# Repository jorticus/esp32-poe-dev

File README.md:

## ESP32 PoE Dev Board

A simple ESP32 ethernet + PoE dev board

WARNING: PoE is NOT ISOLATED! Be careful what you attach.

See [jared.geek.nz/esp32-poe-devboard](jared.geek.nz/esp32-poe-devboard) for the story.

## Usage

### ESPHome

```yaml
esp32:
  board: esp32dev

ethernet:
  type:     RTL8201
  mdc_pin:  GPIO23
  mdio_pin: GPIO18
  clk_mode: GPIO0_OUT
  phy_addr: 0

...
```

### Arduino

`main.cpp`
```cpp
void setup() {
    // WiFi antenna not available on this board
    WiFi.mode(WIFI_OFF); 

    ETH.begin();
    ETH.config();
}
```

`platformio.ini`
```ini
[platformio]

[env:esp32_poe]
platform  = espressif32
framework = arduino
board     = esp32_dev
build_flags = 
    -DETH_PHY_ADDR=0
    -DETH_PHY_MDC=23
    -DETH_PHY_MDIO=18
    -DETH_PHY_TYPE=ETH_PHY_RTL8201
    -DETH_CLK_MODE=ETH_CLOCK_GPIO0_OUT

```

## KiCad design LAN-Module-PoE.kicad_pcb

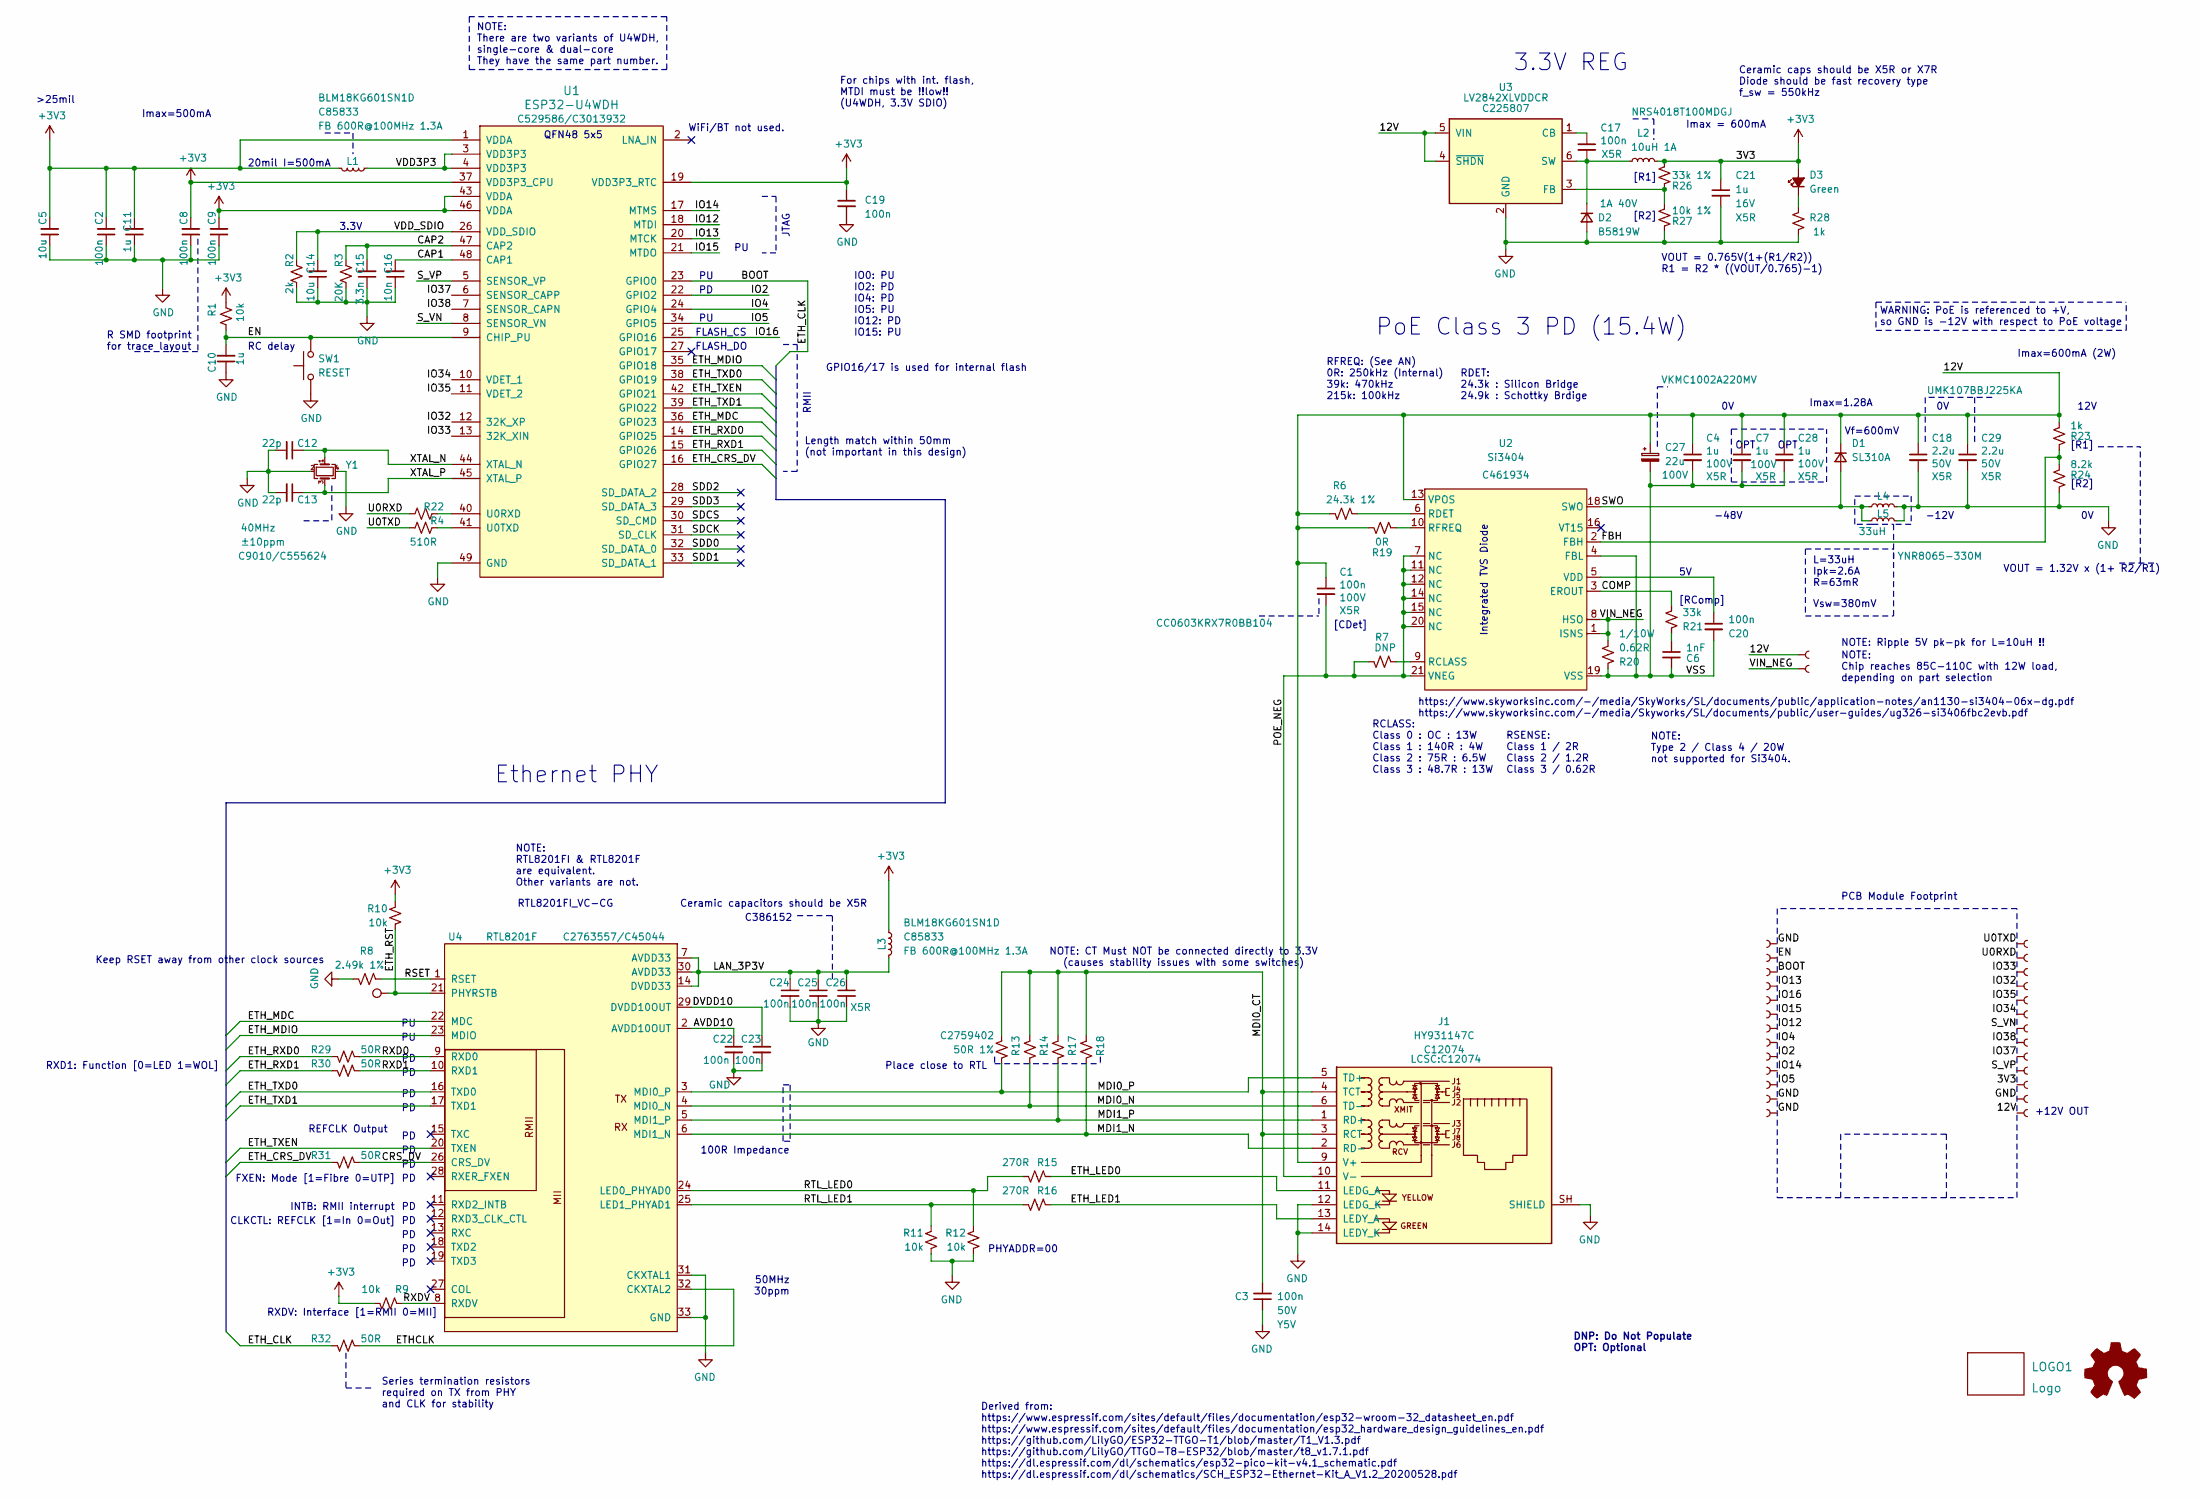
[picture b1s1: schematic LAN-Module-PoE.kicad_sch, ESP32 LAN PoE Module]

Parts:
C1: 100n; C_0603_1608Metric; Part CC0603KRX7R0BB104; LCSC C113803
C2, C3, C9, C17, C19, C20, C23, C24, C25, C26: 100n; C_0603_1608Metric
C4: 1u; C_0805_2012Metric; Part HMK212BC7105KGHTE; LCSC C385977
C5, C14: 10u; C_0603_1608Metric
C6: 1nF; C_0603_1608Metric
C7, C10, C11, C21, C28: 1u; C_0603_1608Metric
C8, C22: 100n; R_0603_1608Metric
C12, C13: 22p; C_0603_1608Metric
C15: 3.3n; C_0603_1608Metric
C16: 10n; C_0603_1608Metric
C18, C29: 2.2u; C_0805_2012Metric; Part UMK107BBJ225KA; LCSC C268016
C27: 22u; C_Elec_6.3x5.4; Part VKMC1002A220MV; LCSC C487431
D1: SL310A; D_SMA
D2: B5819W; D_SOD-123; Rating 1A 40V; LCSC C2685454
D3: Green; LED_0603_1608Metric
J1: HY931147C; RJ45_Wuerth_7499111446_Horizontal; Part LCSC:C12074; LCSC C12074
J2, J3, J4, J5, J6, J7, J8, J9, J10, J11, J12, J13, J14, J15, J16, J17, J18, J19, J20, J21, J22, J23, J24, J25, J26, J27, J28, J29: ProtoCastellatedHeader; ProtoHeader_65mil
L1, L3: FB 600R@100MHz 1.3A; R_0603_1608Metric; Part BLM18KG601SN1D; LCSC C85833
L2: 10uH 1A; L_Taiyo-Yuden_NR-40xx; Part NRS4018T100MDGJ; LCSC C222882
L4: 33uH; L_Taiyo-Yuden_NR-80xx_HandSoldering; Rating 1.2A; Part YNR8065-330M; LCSC C2681905
L5: -; L_Taiyo-Yuden_NR-60xx
LOGO1: Logo; wolfpaw-0.3
R1, R9, R10, R11, R12: 10k; R_0603_1608Metric
R2: 2k; R_0603_1608Metric
R3: 20K; R_0603_1608Metric
R4, R22: 510R; R_0603_1608Metric
R6: 24.3k 1%; R_0603_1608Metric; LCSC C2930079
R7: DNP; R_0603_1608Metric
R8: 2.49k 1%; R_0603_1608Metric; LCSC C2930072
R13: 50R 1%; R_0603_1608Metric; Tolerance 1%; LCSC C2759402
R14, R17: 50R 1%; R_0603_1608Metric; Tolerance 1%
R15, R16: 270R; R_0603_1608Metric
R18: 50R 1%; R_0603_1608Metric
R19: 0R; R_0603_1608Metric
R20: 0.62R; R_0805_2012Metric; LCSC C2930222
R21: 33k; R_0603_1608Metric
R23: 1k; R_0603_1608Metric; LCSC C22548
R24: 8.2k; R_0603_1608Metric; LCSC C114637
R26: 33k 1%; R_0603_1608Metric; LCSC C126359
R27: 10k 1%; R_0603_1608Metric; LCSC C98220
R28: 1k; R_0603_1608Metric
R29, R30, R31, R32: 50R; R_0603_1608Metric
SW1: RESET; SW_Push_SPST_NO_Alps_SKRK
TP1: TP; TP-1MM
U1: ESP32-U4WDH; QFN-48-1EP_5x5mm_P0.35mm_EP3.7x3.7mm_ThermalVias; LCSC C529586/C3013932
U2: Si3404; QFN-20-1EP_4x4mm_P0.5mm_EP2.6x2.6mm; LCSC C461934
U3: LV2842XLVDDCR; SOT-23-6; LCSC C225807
U4: RTL8201F; QFN-32-1EP_5x5mm_P0.5mm_EP3.1x3.1mm; LCSC C2763557/C45044
Y1: 40MHz; Crystal_SMD_3225-4Pin_3.2x2.5mm; LCSC C9010/C555624

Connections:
+3V3: C2.2, C5.2, C8.2, C9.2, C11.2, C19.1, C21.1, D3.2 (A), J15.1, L1.2, L2.2, L3.1, R1.2, R9.1, R10.1, R26.2, U1.1 (VDDA), U1.19 (VDD3P3_RTC), U1.37 (VDD3P3_CPU), U1.43 (VDDA), U1.46 (VDDA)
/12V: C1.1, C4.1, C7.1, C18.1, C27.1, C28.1, C29.1, D1.1 (K), J1.9 (V+), J2.1, J28.1, R6.1, R19.1, R23.2, U2.13 (VPOS), U3.4 (~SHDN), U3.5 (VIN)
/AVDD10: C22.1, U4.2 (AVDD10OUT)
/BOOT: J5.1, R32.1, U1.23 (GPIO0)
/CAP1: C16.2, U1.48 (CAP1)
/CAP2: C15.2, R3.2, U1.47 (CAP2)
/COMP: R21.2, U2.3 (EROUT)
/CRS_DV: R31.2, U4.26 (CRS_DV)
/DVDD10: C23.1, U4.29 (DVDD10OUT)
/EN: C10.2, J4.1, R1.1, SW1.2, U1.9 (CHIP_PU)
/ETHCLK: R32.2, U4.32 (CKXTAL2)
/ETH_CRS_DV: R31.1, U1.16 (GPIO27)
/ETH_LED0: J1.11 (LEDG_A), R15.2
/ETH_LED1: J1.13 (LEDY_A), R16.2
/ETH_MDC: U1.36 (GPIO23), U4.22 (MDC)
/ETH_MDIO: U1.35 (GPIO18), U4.23 (MDIO)
/ETH_RST: R10.2, TP1.1, U4.21 (PHYRSTB)
/ETH_RXD0: R29.1, U1.14 (GPIO25)
/ETH_RXD1: R30.1, U1.15 (GPIO26)
/ETH_TXD0: U1.38 (GPIO19), U4.16 (TXD0)
/ETH_TXD1: U1.39 (GPIO22), U4.17 (TXD1)
/ETH_TXEN: U1.42 (GPIO21), U4.20 (TXEN)
/FBH: R23.1, R24.2, U2.2 (FBH)
/IO2: J11.1, U1.22 (GPIO2)
/IO4: J10.1, U1.24 (GPIO4)
/IO5: J13.1, U1.34 (GPIO5)
/IO12: J9.1, U1.18 (MTDI)
/IO13: J6.1, U1.20 (MTCK)
/IO14: J12.1, U1.17 (MTMS)
/IO15: J8.1, U1.21 (MTDO)
/IO16: J7.1, U1.25 (GPIO16)
/IO32: J20.1, U1.12 (32K_XP)
/IO33: J19.1, U1.13 (32K_XIN)
/IO34: J22.1, U1.10 (VDET_1)
/IO35: J21.1, U1.11 (VDET_2)
/IO37: J25.1, U1.6 (SENSOR_CAPP)
/IO38: J24.1, U1.7 (SENSOR_CAPN)
/LAN_3P3V: C24.1, C25.1, C26.1, L3.2, U4.7 (AVDD33), U4.14 (DVDD33), U4.30 (AVDD33)
/MDI0_CT: C3.2, J1.3 (RCT), J1.4 (TCT), R13.1, R14.1, R17.1, R18.1
/MDI0_N: J1.6 (TD-), R14.2, U4.4 (MDI0_N)
/MDI0_P: J1.5 (TD+), R13.2, U4.3 (MDI0_P)
/MDI1_N: J1.2 (RD-), R18.2, U4.6 (MDI1_N)
/MDI1_P: J1.1 (RD+), R17.2, U4.5 (MDI1_P)
/POE_NEG: C1.2, J1.10 (V-), R7.1, U2.7 (NC), U2.11 (NC), U2.12 (NC), U2.14 (NC), U2.15 (NC), U2.20 (NC), U2.21 (VNEG)
/RSET: R8.2, U4.1 (RSET)
/RTL_LED0: R12.1, R15.1, U4.24 (LED0_PHYAD0)
/RTL_LED1: R11.1, R16.1, U4.25 (LED1_PHYAD1)
/RXD0: R29.2, U4.9 (RXD0)
/RXD1: R30.2, U4.10 (RXD1)
/RXDV: R9.2, U4.8 (RXDV)
/SDCK: U1.31 (SD_CLK)
/SDCS: U1.30 (SD_CMD)
/SDD0: U1.32 (SD_DATA_0)
/SDD1: U1.33 (SD_DATA_1)
/SDD2: U1.28 (SD_DATA_2)
/SDD3: U1.29 (SD_DATA_3)
/SWO: D1.2 (A), L4.1, L5.1, U2.18 (SWO)
/S_VN: J23.1, U1.8 (SENSOR_VN)
/S_VP: J26.1, U1.5 (SENSOR_VP)
/U0RXD: J18.1, R22.1
/U0TXD: J17.1, R4.1
/VDD3P3: L1.1, U1.3 (VDD3P3), U1.4 (VDD3P3)
/VDD_SDIO: C14.2, R2.2, U1.26 (VDD_SDIO)
/VIN_NEG: J29.1, R20.2, U2.1 (ISNS), U2.8 (HSO)
/VSS: C4.2, C6.2, C7.2, C20.2, C27.2, C28.2, R20.1, U2.4 (FBL), U2.19 (VSS)
/XTAL_N: C12.1, U1.44 (XTAL_N), Y1.1
/XTAL_P: C13.1, U1.45 (XTAL_P), Y1.3
GND: C2.1, C3.1, C5.1, C8.1, C9.1, C10.1, C11.1, C12.2, C13.2, C14.1, C15.1, C16.1, C18.2, C19.2, C21.2, C22.2, C23.2, C24.2, C25.2, C26.2, C29.2, D2.2 (A), J1.12 (LEDG_K), J1.14 (LEDY_K), J1.SH (SHIELD), J3.1, J14.1, J16.1, J27.1, L4.2, L5.2, R2.1, R3.1, R8.1, R11.2, R12.2, R24.1, R27.1, R28.1, SW1.1, U1.49 (GND), U3.2 (GND), U4.31 (CKXTAL1), U4.33 (GND), Y1.2, Y1.4
unnamed: C6.1, R21.1
unnamed: C17.2, D2.1 (K), L2.1, U3.6 (SW)
unnamed: D3.1 (K), R28.2
unnamed: R22.2, U1.40 (U0RXD)
unnamed: R4.2, U1.41 (U0TXD)
unnamed: R7.2, U2.9 (RCLASS)
unnamed: R6.2, U2.6 (RDET)
unnamed: R19.2, U2.10 (RFREQ)
unnamed: C20.1, U2.5 (VDD)
unnamed: C17.1, U3.1 (CB)
unnamed: R26.1, R27.2, U3.3 (FB)

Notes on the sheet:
3.3V
IO0: PU IO2: PD IO4: PD IO5: PU IO12: PD IO15: PU
QFN48 5x5
50MHz 30ppm
https://www.skyworksinc.com/-/media/SkyWorks/SL/documents/public/application-notes/an1130-si3404-06x-dg.pdf https://www.skyworksinc.com/-/media/Skyworks/SL/documents/public/user-guides/ug326-si3406fbc2evb.pdf
OPT
Keep RSET away from other clock sources
12V
Derived from: https://www.espressif.com/sites/default/files/documentation/esp32-wroom-32_datasheet_en.pdf https://www.espressif.com/sites/default/files/documentation/esp32_hardware_design_guidelines_en.pdf https://github.com/LilyGO/ESP32-TTGO-T1/blob/master/T1_V1.3.pdf https://github.com/LilyGO/TTG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
I=500mA
RDET: 24.3k : Silicon Bridge 24.9k : Schottky Brdige
Vsw=380mV
Integrated TVS Diode
>25mil
-12V
Ceramic caps should be X5R or X7R Diode should be fast recovery type f_sw = 550kHz
WiFi/BT not used.
+12V OUT
GPIO16/17 is used for internal flash
20mil
NOTE: Ripple 5V pk-pk for L=10uH !!
[R1]
DNP: Do Not Populate OPT: Optional
[RComp]
C386152
NOTE: There are two variants of U4WDH, single-core & dual-core They have the same part number.
NOTE: CT Must NOT be connected directly to 3.3V (causes stability issues with some switches)
Series termination resistors required on TX from PHY and CLK for stability
Ceramic capacitors should be X5R
Imax = 600mA
Imax=600mA (2W)
NOTE: Type 2 / Class 4 / 20W not supported for Si3404.
PCB Module Footprint
RC delay
[R2]
RXD1: Function [0=LED 1=WOL]
RSENSE: Class 1 / 2R Class 2 / 1.2R Class 3 / 0.62R
INTB: RMII interrupt
RCLASS: Class 0 : OC : 13W Class 1 : 140R : 4W Class 2 : 75R : 6.5W Class 3 : 48.7R : 13W
FLASH_CS

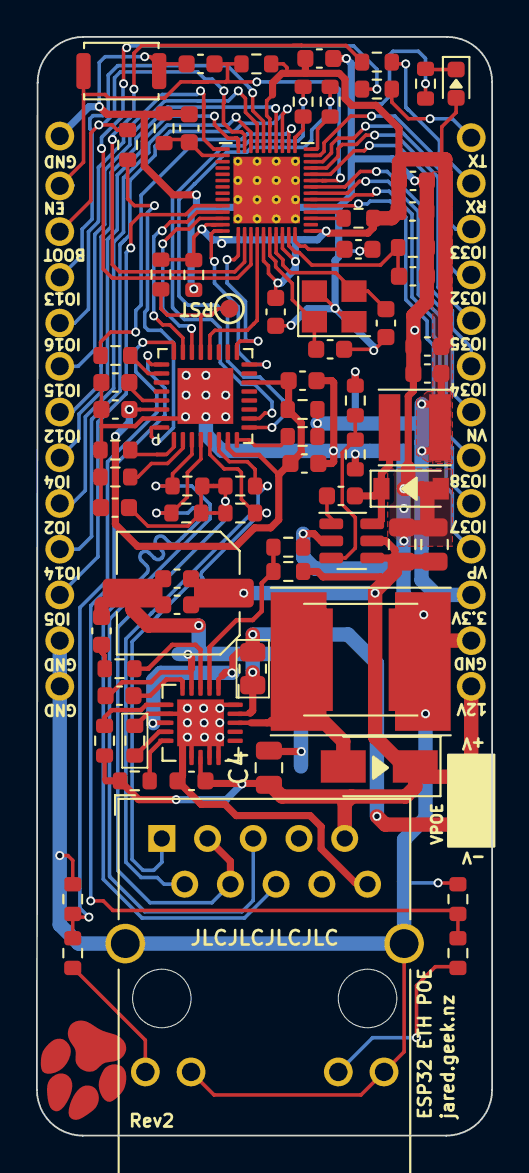
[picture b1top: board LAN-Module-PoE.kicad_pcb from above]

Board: 2 copper layers, 25.3 x 61.0 mm, 104 parts (0 on the bottom side), 73 nets.

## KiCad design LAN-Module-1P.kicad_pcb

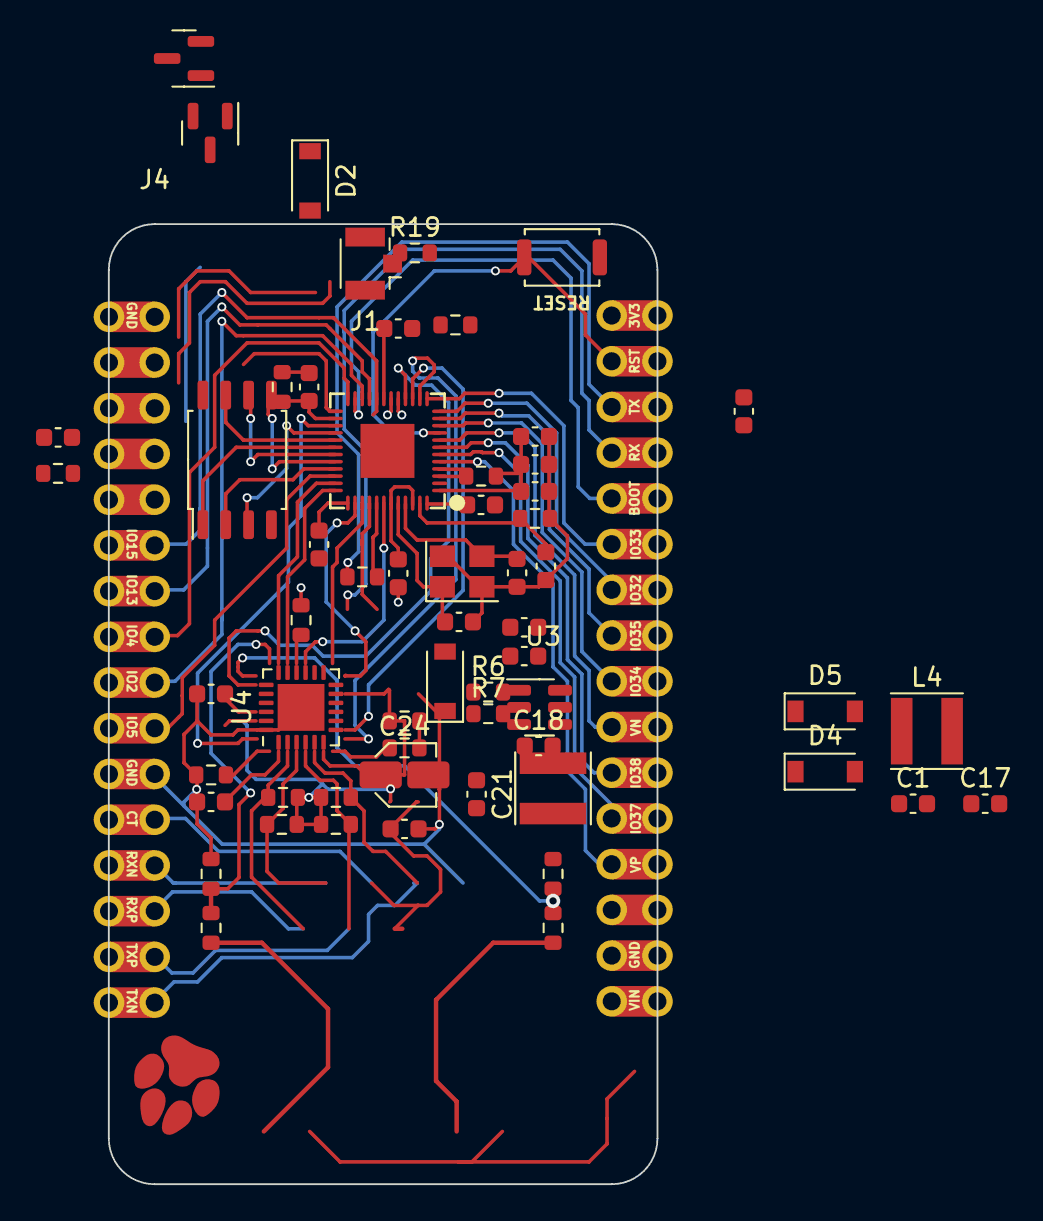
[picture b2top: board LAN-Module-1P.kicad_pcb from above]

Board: 2 copper layers, 30.5 x 53.3 mm, 62 parts (0 on the bottom side), 50 nets.

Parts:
C1, C5, C6, C7, C17, C19, C22, C23: 100n; C_0603_1608Metric
C2, C8, C9: 1u; C_0603_1608Metric
C3, C4: 10u; C_0603_1608Metric
C10, C11: 22p; C_0603_1608Metric
C12: 4.7u; C_0603_1608Metric
C13, C15: 3.3n; C_0603_1608Metric
C14, C16: 10n; C_0603_1608Metric
C18, C21: 2.2u; C_0603_1608Metric
C24: 4.7u; C_Elec_3x5.4
D1, D2, D4, D5: FM240W; D_SOD-123
J1: ANT; U.FL_Hirose_U.FL-R-SMT-1_Vertical
J4: Conn_Left; ProtoCastellatedHeader_1x16
J5: Conn_Right; ProtoCastellatedHeader_1x16
L1, L3: FB 600R@100MHz 1.3A; R_0603_1608Metric
L2, L4: 10uH 1A; L_Taiyo-Yuden_NR-40xx
LOGO1: Logo; wolfpaw-0.3
Q1, Q2: 2N7002; SOT-23
R1, R5, R6, R10, R11, R12, R15: 10k; R_0603_1608Metric
R2: 2k; R_0603_1608Metric
R3: 20K; R_0603_1608Metric
R4: 2.49k 1%; R_0603_1608Metric
R7, R8: 499R; R_0603_1608Metric
R9: 10K; R_0603_1608Metric
R13: 22k; R_0603_1608Metric
R14: 47k; R_0603_1608Metric
R16: 33k 1%; R_0603_1608Metric
R17: 10k 1%; R_0603_1608Metric
R18, R19: 0R; R_0603_1608Metric
SW1: RESET; SW_Push_SPST_NO_Alps_SKRK
U1: ESP32-U4WDH; ESP32-REDUCED
U2: W25Q32; SOIC-8_5.23x5.23mm_P1.27mm
U3: LV2842XLVDDCR; SOT-23-6
U4: CP2102N-Axx-xQFN24; QFN-24-1EP_4x4mm_P0.5mm_EP2.6x2.6mm
Y1: 40MHz ±10ppm; Crystal_SMD_3225-4Pin_3.2x2.5mm

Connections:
+3V3: C1.2, C2.2, C3.2, C4.2, C5.2, C6.2, C7.2, C9.2, C17.1, C19.1, C22.2, C24.1, L1.2, L2.2, L4.2, R1.2, R9.2, R15.2, R16.1, U1.1 (VDDA), U1.19 (VDD3P3_RTC), U1.37 (VDD3P3_CPU), U1.43 (VDDA), U1.46 (VDDA), U2.8 (VCC), U4.5 (VIO), U4.6 (VDD), U4.7 (VREGIN)
/BOOT: J5.5, R18.2, U1.23 (GPIO0)
/CAP1: C14.2, C16.2, U1.48 (CAP1)
/CAP2: C13.2, C15.2, R3.2, U1.47 (CAP2)
/EN: C8.2, J5.2, R1.1, R19.2, SW1.2, U1.9 (CHIP_PU)
/ETH_RST: R6.2, R10.2
/IO2: J4.9, U1.22 (GPIO2)
/IO4: J4.8, U1.24 (GPIO4)
/IO5: J4.10, U1.34 (GPIO5)
/IO12: J4.3, R9.1, U1.18 (MTDI)
/IO13: J4.6, U1.20 (MTCK)
/IO14: J4.4, U1.17 (MTMS)
/IO15: J4.7, U1.21 (MTDO)
/IO16: J4.2, U1.25 (GPIO16)
/IO32: J5.7, U1.12 (32K_XP)
/IO33: J5.6, U1.13 (32K_XIN)
/IO34: J5.9, U1.10 (VDET_1)
/IO35: J5.8, U1.11 (VDET_2)
/IO37: J5.12, U1.6 (SENSOR_CAPP)
/IO38: J5.11, U1.7 (SENSOR_CAPN)
/SDCK: U1.31 (SD_CLK), U2.6 (CLK)
/SDCS: U1.30 (SD_CMD), U2.1 (~CS)
/SDD0: U1.32 (SD_DATA_0), U2.5 (DI(IO0))
/SDD1: U1.33 (SD_DATA_1), U2.2 (DO(IO1))
/SDD2: U1.28 (SD_DATA_2), U2.3 (IO2)
/SDD3: U1.29 (SD_DATA_3), U2.7 (IO3)
/S_VN: J5.10, U1.8 (SENSOR_VN)
/S_VP: J5.13, U1.5 (SENSOR_VP)
/U0RXD: J5.4, R7.1, U4.21 (TXD)
/U0TXD: J5.3, R8.1, U4.20 (RXD)
/VDD3P3: L1.1, U1.3 (VDD3P3), U1.4 (VDD3P3)
/VDD_SDIO: C12.2, R2.2, U1.26 (VDD_SDIO)
/XTAL_N: C10.1, U1.44 (XTAL_N), Y1.1
/XTAL_P: C11.1, U1.45 (XTAL_P), Y1.3
GND: C1.1, C2.1, C3.1, C4.1, C5.1, C6.1, C7.1, C8.1, C9.1, C10.2, C11.2, C12.1, C13.1, C14.1, C15.1, C16.1, C17.2, C18.2, C19.2, C21.2, C22.1, C24.2, D1.2 (A), D5.2 (A), J1.2 (Ext), J4.1, J4.11, J5.15, R2.1, R3.1, R4.1, R11.2, R12.2, R14.1, R17.2, SW1.1, U1.49 (GND), U2.4 (GND), U3.2 (GND), U4.2 (GND), U4.25 (GND), Y1.2, Y1.4
unnamed: D1.1 (K), L2.1
unnamed: C23.1, U3.1 (CB)
unnamed: C23.2, D5.1 (K), L4.1, U3.6 (SW)
unnamed: J1.1 (In), U1.2 (LNA_IN)
unnamed: Q1.1 (G), Q2.2 (S), U4.19 (~RTS)
unnamed: Q1.2 (S), R18.1
unnamed: Q1.3 (D), Q2.1 (G), U4.23 (~DTR)
unnamed: Q2.3 (D), R19.1
unnamed: R7.2, U1.40 (U0RXD)
unnamed: R8.2, U1.41 (U0TXD)
unnamed: R13.1, R14.2, U4.8 (VBUS)
unnamed: R15.1, U4.9 (~RST)
unnamed: R16.2, R17.1, U3.3 (FB)
VBUS: D2.2 (A), D4.2 (A), R13.2
VDD: C18.1, C21.1, D2.1 (K), D4.1 (K), L3.1, R5.1, R6.1, R10.1, U3.4 (~SHDN), U3.5 (VIN)

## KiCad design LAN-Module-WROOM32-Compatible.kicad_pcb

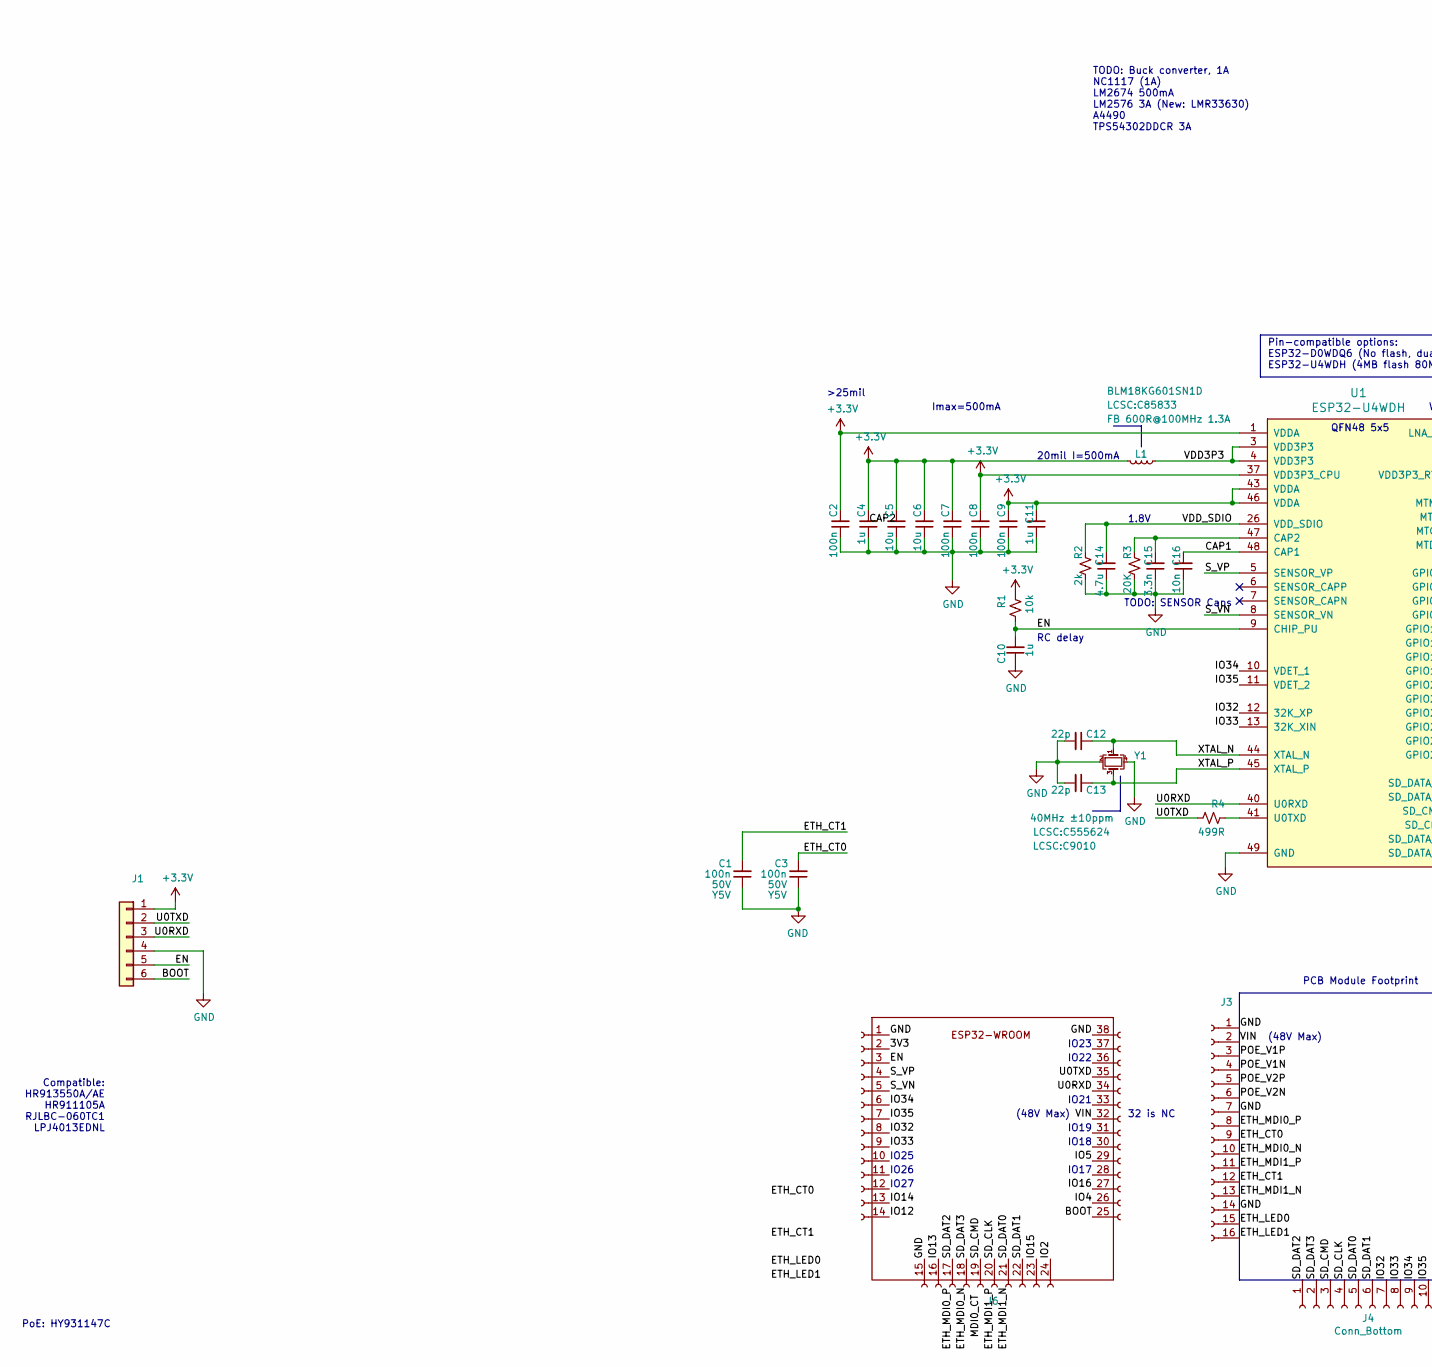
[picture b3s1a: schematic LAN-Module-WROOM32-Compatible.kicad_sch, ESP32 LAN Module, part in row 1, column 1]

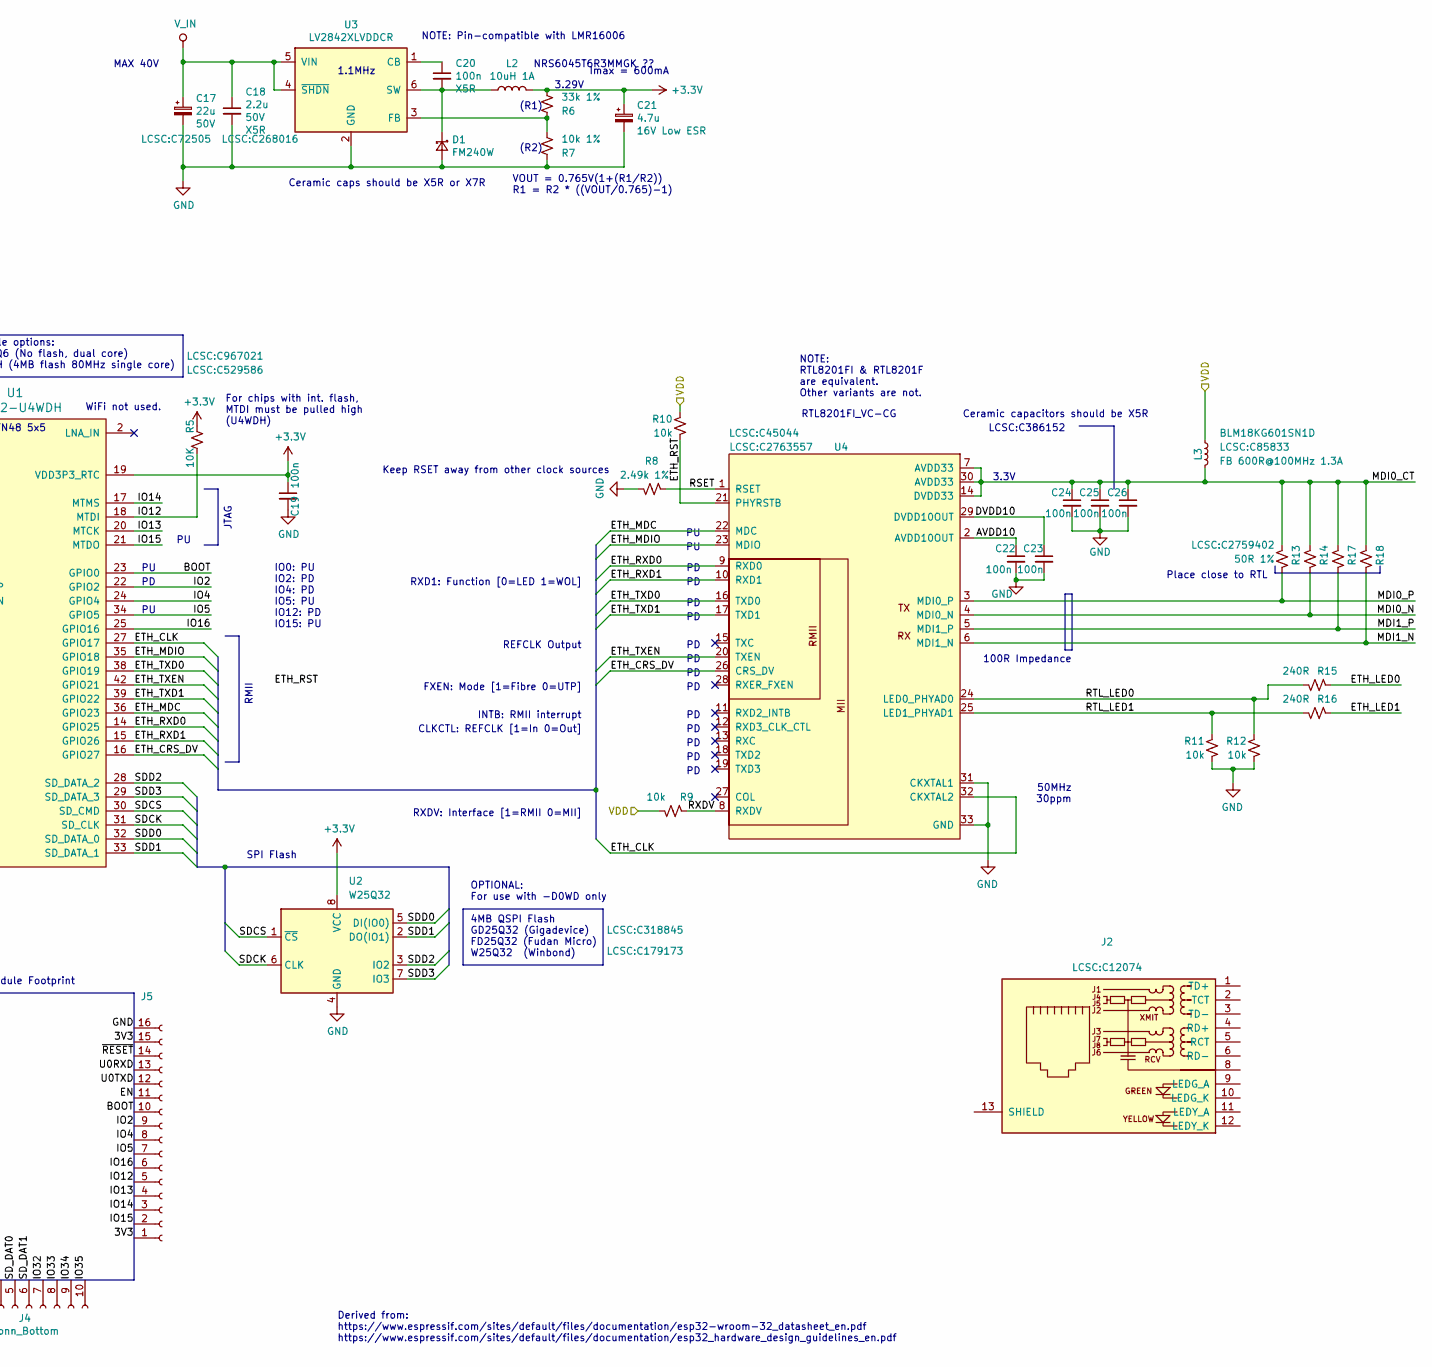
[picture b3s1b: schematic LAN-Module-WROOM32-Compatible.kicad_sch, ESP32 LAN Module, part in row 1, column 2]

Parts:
C1, C3: 100n; C_0603_1608Metric; Rating 50V
C2, C7, C8, C9, C19, C20, C22, C23, C24, C25, C26: 100n; C_0603_1608Metric
C4, C10, C11: 1u; C_0805_2012Metric
C5, C6: 10u; C_Elec_3x5.4
C12, C13: 22p; C_0603_1608Metric
C14, C21: 4.7u; C_Elec_3x5.4
C15: 3.3n; C_0603_1608Metric
C16: 10n; C_0603_1608Metric
C17: 22u; C_Elec_6.3x5.4; Part1 LCSC:C72505
C18: 2.2u; C_0603_1608Metric; Part1 LCSC:C268016
D1: FM240W; D_SMA
J1, J3, J5, J6: (no value)
J2: Part LCSC:C12074
J4: Conn_Bottom
L1, L3: FB 600R@100MHz 1.3A; R_0805_2012Metric_Pad1.20x1.40mm_HandSolder; Part1 LCSC:C85833
L2: 10uH 1A; L_Taiyo-Yuden_NR-40xx
R1, R9, R10, R11, R12: 10k; R_0603_1608Metric
R2: 2k; R_0603_1608Metric
R3: 20K; R_0603_1608Metric
R4: 499R; R_0603_1608Metric
R5: 10K; R_0603_1608Metric
R6: 33k 1%; R_0603_1608Metric
R7: 10k 1%; R_0603_1608Metric
R8: 2.49k 1%; R_0603_1608Metric
R13: 50R 1%; R_0603_1608Metric; Part LCSC:C2759402
R14, R17, R18: 49.9R 1%; R_0603_1608Metric
R15, R16: 240R; R_0603_1608Metric
U1: ESP32-U4WDH; ESP32-REDUCED; Part1 LCSC:C529586
U2: W25Q32; SOIC-8_5.23x5.23mm_P1.27mm; Part LCSC:C179173
U3: LV2842XLVDDCR; SOT-23-6
U4: Part1 LCSC:C2763557
Y1: 40MHz ±10ppm; Crystal_SMD_3225-4Pin_3.2x2.5mm_HandSoldering; Part1 LCSC:C9010

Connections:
+3V3: C2.2, C4.2, C5.2, C6.2, C7.2, C8.2, C9.2, C11.2, C19.1, C21.1, J1.1, L1.2, L2.2, R1.2, R5.2, R6.1, U1.1 (VDDA), U1.19 (VDD3P3_RTC), U1.37 (VDD3P3_CPU), U1.43 (VDDA), U1.46 (VDDA), U2.8 (VCC)
/3V3: J5.1, J5.15, J6.2
/AVDD10: C22.1, U4.2 (AVDD10OUT)
/BOOT: J1.6, J5.10, J6.25, U1.23 (GPIO0)
/CAP1: C16.2, U1.48 (CAP1)
/DVDD10: C23.1, U4.29 (DVDD10OUT)
/EN: C10.2, J1.5, J5.11, J6.3, R1.1, U1.9 (CHIP_PU)
/ETH_CLK: U1.27 (GPIO17), U4.32 (CKXTAL2)
/ETH_CRS_DV: U1.16 (GPIO27), U4.26 (CRS_DV)
/ETH_CT0: C3.2, J3.9
/ETH_CT1: C1.2, J3.12
/ETH_LED0: J3.15, R15.2
/ETH_LED1: J3.16, R16.2
/ETH_MDC: U1.36 (GPIO23), U4.22 (MDC)
/ETH_MDI0_N: J3.10
/ETH_MDI0_P: J3.8
/ETH_MDI1_N: J3.13
/ETH_MDI1_P: J3.11
/ETH_MDIO: U1.35 (GPIO18), U4.23 (MDIO)
/ETH_RST: R10.2, U4.21 (PHYRSTB)
/ETH_RXD0: U1.14 (GPIO25), U4.9 (RXD0)
/ETH_RXD1: U1.15 (GPIO26), U4.10 (RXD1)
/ETH_TXD0: U1.38 (GPIO19), U4.16 (TXD0)
/ETH_TXD1: U1.39 (GPIO22), U4.17 (TXD1)
/ETH_TXEN: U1.42 (GPIO21), U4.20 (TXEN)
/IO2: J5.9, J6.24, U1.22 (GPIO2)
/IO4: J5.8, J6.26, U1.24 (GPIO4)
/IO5: J5.7, J6.29, U1.34 (GPIO5)
/IO12: J5.5, J6.14, R5.1, U1.18 (MTDI)
/IO13: J5.4, J6.16, U1.20 (MTCK)
/IO14: J5.3, J6.13, U1.17 (MTMS)
/IO15: J5.2, J6.23, U1.21 (MTDO)
/IO16: J5.6, J6.27, U1.25 (GPIO16)
/IO32: J4.7, J6.8, U1.12 (32K_XP)
/IO33: J4.8, J6.9, U1.13 (32K_XIN)
/IO34: J4.9, J6.6, U1.10 (VDET_1)
/IO35: J4.10, J6.7, U1.11 (VDET_2)
/MDI0_CT: C24.1, C25.1, C26.1, L3.2, R13.1, R14.1, R17.1, R18.1, U4.7 (AVDD33), U4.14 (DVDD33), U4.30 (AVDD33)
/MDI0_N: R14.2, U4.4 (MDI0_N)
/MDI0_P: R13.2, U4.3 (MDI0_P)
/MDI1_N: R18.2, U4.6 (MDI1_N)
/MDI1_P: R17.2, U4.5 (MDI1_P)
/POE_V1N: J3.4
/POE_V1P: J3.3
/POE_V2N: J3.6
/POE_V2P: J3.5
/RSET: R8.2, U4.1 (RSET)
/RTL_LED0: R12.1, R15.1, U4.24 (LED0_PHYAD0)
/RTL_LED1: R11.1, R16.1, U4.25 (LED1_PHYAD1)
/RXDV: R9.2, U4.8 (RXDV)
/SDCK: U1.31 (SD_CLK), U2.6 (CLK)
/SDCS: U1.30 (SD_CMD), U2.1 (~CS)
/SDD0: U1.32 (SD_DATA_0), U2.5 (DI(IO0))
/SDD1: U1.33 (SD_DATA_1), U2.2 (DO(IO1))
/SDD2: U1.28 (SD_DATA_2), U2.3 (IO2)
/SDD3: U1.29 (SD_DATA_3), U2.7 (IO3)
/SD_CLK: J4.4, J6.20
/SD_CMD: J4.3, J6.19
/SD_DAT0: J4.5, J6.21
/SD_DAT1: J4.6, J6.22
/SD_DAT2: J4.1, J6.17
/SD_DAT3: J4.2, J6.18
/S_VN: J6.5, U1.8 (SENSOR_VN)
/S_VP: J6.4, U1.5 (SENSOR_VP)
/U0RXD: J1.3, J5.13, J6.34, U1.40 (U0RXD)
/U0TXD: J1.2, J5.12, J6.35, R4.1
/VDD3P3: L1.1, U1.3 (VDD3P3), U1.4 (VDD3P3)
/VDD_SDIO: C14.2, R2.2, U1.26 (VDD_SDIO)
/VIN: J3.2, J6.32
/XTAL_N: C12.1, U1.44 (XTAL_N), Y1.1
/XTAL_P: C13.1, U1.45 (XTAL_P), Y1.3
/~RESET: J5.14
GND: C1.1, C2.1, C3.1, C4.1, C5.1, C6.1, C7.1, C8.1, C9.1, C10.1, C11.1, C12.2, C13.2, C14.1, C15.1, C16.1, C17.2, C18.2, C19.2, C21.2, C22.2, C23.2, C24.2, C25.2, C26.2, D1.2 (A), J1.4, J3.1, J3.7, J3.14, J5.16, J6.1, J6.15, J6.38, R2.1, R3.1, R7.2, R8.1, R11.2, R12.2, U1.49 (GND), U2.4 (GND), U3.2 (GND), U4.31 (CKXTAL1), U4.33 (GND), Y1.2, Y1.4
unnamed: C15.2, R3.2, U1.47 (CAP2)
unnamed: C20.1, U3.1 (CB)
unnamed: C20.2, D1.1 (K), L2.1, U3.6 (SW)
unnamed: R4.2, U1.41 (U0TXD)
unnamed: R6.2, R7.1, U3.3 (FB)
VDD: C17.1, C18.1, L3.1, R9.1, R10.1, U3.4 (~SHDN), U3.5 (VIN)

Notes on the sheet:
IO17
1.8V
TODO: SENSOR Caps
IO0: PU IO2: PD IO4: PD IO5: PU IO12: PD IO15: PU
IO23
QFN48 5x5
1.1MHz
50MHz 30ppm
IO18
Keep RSET away from other clock sources
Derived from: https://www.espressif.com/sites/default/files/documentation/esp32-wroom-32_datasheet_en.pdf https://www.espressif.com/sites/default/files/documentation/esp32_hardware_design_guidelines_en.pdf
I=500mA
IO26
OPTIONAL: For use with -D0WD only 4MB QSPI Flash GD25Q32 (Gigadevice) FD25Q32 (Fudan Micro) W25Q32 (Winbond)
IO19
TODO: Buck converter, 1A NC1117 (1A) LM2674 500mA LM2576 3A (New: LMR33630) A4490 TPS54302DDCR 3A
>25mil
NRS6045T6R3MMGK ??
MAX 40V
(48V Max)
WiFi not used.
VOUT = 0.765V(1+(R1/R2)) R1 = R2 * ((VOUT/0.765)-1)
(R1)
20mil
Imax = 600mA
32 is NC
LCSC:C386152
PoE: HY931147C
Ceramic caps should be X5R or X7R
Compatible: HR913550A/AE HR911105A RJLBC-060TC1 LPJ4013EDNL
3.3V
Pin-compatible options: ESP32-D0WDQ6 (No flash, dual core) ESP32-U4WDH (4MB flash 80MHz single core)
Ceramic capacitors should be X5R
PCB Module Footprint
RC delay
RXD1: Function [0=LED 1=WOL]
IO27
NOTE: Pin-compatible with LMR16006
INTB: RMII interrupt
JTAG

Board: 2 copper layers, 57 parts (0 on the bottom side), 64 nets, no tracks yet.

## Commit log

2022-09-16 Layout PCB
2022-10-29 Final routing and placement
2022-10-30 Address TODOs
2022-10-30 Generate gerbers r1
2022-10-30 Add PoE variant
2022-10-30 Add 1Pair Ethernet Variant (WIP)
2022-11-09 Final revision of PoE variant
2022-11-18 Fix footprint for ESP32 (QFN 5x5), add heat pad for PoE regulator
2022-11-18 Re-layout with narrower board outline (-0.1")
2022-11-20 Finalize layout for rev2
2022-12-03 Gerbers for manufacture, rev2
2022-12-03 Final PoE design with fixes for rev2 gerber spin
    - MTDI must not be pulled high
    - GPIO17 for PHY clock conflicts with internal flash
2022-12-03 Add sample firmware for ETH-POE
2022-12-04 Update LCSC part numbers and adjust component values to available parts
2025-02-28 Add sample ESPHome config
2025-02-28 Rev2.1 changes
    Just changing component attributes, no design changes
2025-02-28 Add license (applies to all previous commits)
2025-02-28 Update kicad project files
2025-02-28 Add variant with castellated holes
2025-02-28 Add README
2025-03-16 Update PoE PCB Kicad version
2025-03-16 HW REV: Fix stability issue
    Important change required to ensure stability across different types of ethernet switches.
    I had only tested this with a TP-LINK switch, but the design did not work with other switches, and the reference schematic does NOT specify that the CT/termination resistors should be tied to 3.3V. I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
